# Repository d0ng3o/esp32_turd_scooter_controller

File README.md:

# Scooter control board

A standalone replacement control board for a **decommissioned Bird One #590AE**
shared e-scooter (the operator went bankrupt), built around a **Seeed XIAO
ESP32-C3**.

**Tested on:** a real **Bird One #590AE**, driving its stock **Nanjing Lishui
LSW6G-RF-FOC** motor controller over the original one-wire bus. Other Bird One
units (and other scooters on the same Lishui colon protocol) are likely
compatible but unverified.

> ⚠️ **Safety-critical, experimental, unofficial.** This board controls a
> vehicle's motor, throttle, and braking behavior. It is provided **as-is, with
> no warranty**, is not certified by anyone, and is not affiliated with or
> endorsed by Bird. Build and ride at your own risk — read
> **[DISCLAIMER.md](DISCLAIMER.md)** first.

The project has two halves:

1. **Reverse-engineering** the scooter's one-wire bus between the original
   control board and the Lishui motor controller — captured and documented so
   the controller can be driven directly.
2. A **custom KiCad control board** that replaces the dead original: same
   harness connector, same bus protocol, plus throttle/brake sensing, pack
   voltage, a buzzer, an addressable status LED, an on-board IMU for
   wake-on-motion, and an OLED display.

## Repository layout

```
.
├── PROTOCOL.md                 the reverse-engineered one-wire bus protocol
├── captures/                   raw bus captures backing PROTOCOL.md
├── esp32-scooter-schematic.html  interactive overview of the board
│
├── scooter_master.py           drive the motor controller as the bus master
├── pi_sniff.py                 passive ride logger (Raspberry Pi, RX-only)
├── bus_experiment.py           scripted bring-up probes
├── bus_listen_poll.py          poll at 50 Hz and log non-echo bytes
├── bus_soak.py                 long idle soak to catch slow telemetry fields
├── install_logger.sh           one-shot Pi logger installer
├── pi-scooter-logger.service   systemd unit for the Pi logger
│
├── firmware/                   the ESP-IDF firmware for the XIAO — see firmware/README.md
└── kicad/                      the hardware — see kicad/README.md
```

## The bus, briefly

Native **3.3 V open-drain half-duplex UART at 115200**. The control board is the
master: it polls the controller at 50 Hz with a colon-framed packet
(`':' TYPE LEN DATA[LEN] CHK CR LF`, `CHK` = XOR of the header+data) carrying the
throttle and light flags, and the controller answers with telemetry. Full frame
types, flags and field map are in **[PROTOCOL.md](PROTOCOL.md)**; it was all
confirmed on hardware (the PC drove the motor across the full throttle range).

## The hardware

The KiCad 10 design lives in **[kicad/](kicad/)** — see
[kicad/README.md](kicad/README.md) for the board overview,
[kicad/board/BOM.md](kicad/board/BOM.md) for the parts and full design
rationale, and [kicad/board/LAYOUT.md](kicad/board/LAYOUT.md) for the layout
playbook. The board is DRC-clean; bare boards and parts have been ordered.

## Status

- ✅ Bus protocol reverse-engineered and documented.
- ✅ Host/Pi tooling to drive and log the bus.
- ✅ Control board schematic + PCB complete, DRC-clean, ordered.
- ✅ ESP32-C3 firmware (ESP-IDF) in **[firmware/](firmware/)** — ride control,
  lights, lock/alarm, IMU wake, OLED UI, WiFi config/OTA; running on hardware.

## Note

The Python at the repo root is **host-side** tooling (PC / Raspberry Pi) used to
reverse-engineer and exercise the bus. It connects to the scooter via a USB
serial adapter (`scooter_master.py`, bench scripts) or a Pi UART (`pi_sniff.py`).
The firmware that runs on the XIAO itself lives in **[firmware/](firmware/)**.

## License

This project is **free/libre and strong-copyleft** — multi-licensed by component,
with each layer under a **share-alike** license. Anyone who copies, modifies, or
builds on it **must release their version under the same license** (no closed or
proprietary forks):

| Component | Files | License |
|---|---|---|
| Code / firmware / scripts | `*.py`, `*.sh`, `*.service` | **GPL-3.0-or-later** — [`LICENSE`](LICENSE) |
| Hardware design (original) | `kicad/board/`, original symbols/footprints | **CERN-OHL-S-2.0** — [`LICENSE-HARDWARE.txt`](LICENSE-HARDWARE.txt) |
| Documentation | `*.md`, BOMs, `esp32-scooter-schematic.html` | **CC-BY-SA-4.0** — [`LICENSE-DOCS.txt`](LICENSE-DOCS.txt) |

Copyright 2026 Taavi Laadung.

**Exception:** the vendor-sourced symbols, footprints, and 3D models under
`kicad/lcsc/` are **not** covered by the above and keep their original
LCSC/EasyEDA/manufacturer terms — see [`kicad/lcsc/README.md`](kicad/lcsc/README.md).

**CERN-OHL-S v2 notice (hardware):** *Copyright 2026 Taavi Laadung. This source
describes Open Hardware and is licensed under the CERN-OHL-S v2. You may
redistribute and modify this source and make products using it under the terms of
the CERN-OHL-S v2 (https://ohwr.org/cern_ohl_s_v2.txt). This source is distributed
WITHOUT ANY EXPRESS OR IMPLIED WARRANTY, INCLUDING OF MERCHANTABILITY,
SATISFACTORY QUALITY AND FITNESS FOR A PARTICULAR PURPOSE. Please see the
CERN-OHL-S v2 for applicable conditions. Source location:*
`https://github.com/d0ng3o/esp32_turd_scooter_controller` *(CERN-OHL-S requires the
source location to be conveyed and, where practicable, kept visible on the product
itself).*

## Disclaimer

See **[DISCLAIMER.md](DISCLAIMER.md)** for the full safety warning and the
"no affiliation" / reverse-engineering notices. In short: this is an
experimental, uncertified board that controls a vehicle — **build and ride at
your own risk**, and check your local road-traffic laws before using it.

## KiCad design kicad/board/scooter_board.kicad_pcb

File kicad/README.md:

# XIAO ESP32-C3 scooter control board — KiCad

Replacement control board for a decommissioned **Bird One #590AE** e-scooter.
A **Seeed XIAO ESP32-C3** reads the throttle and brake, talks to the Lishui
motor controller over the scooter's native **one-wire 3.3 V open-drain UART**
(115200), senses pack voltage, drives a buzzer and an addressable status LED,
carries an on-board IMU for wake-on-motion, and shows telemetry on an
enclosure-mounted OLED.

Designed in **KiCad 10**.

## Layout

```
kicad/
├── board/
│   ├── scooter_board.kicad_pro   project
│   ├── scooter_board.kicad_sch   schematic  ─┐ source of truth
│   ├── scooter_board.kicad_pcb   PCB         ─┘
│   ├── BOM.md                    bill of materials + full design rationale
│   ├── LAYOUT.md                 placement/routing playbook
│   ├── fp-lib-table              points at ../lcsc (the project footprint lib)
│   └── fabrication-toolkit-options.json
├── lcsc/                         project-local parts (LCSC-sourced)
│   ├── scooter_lcsc.kicad_sym    symbols
│   ├── scooter_lcsc.pretty/      footprints (6, all used by the board)
│   └── scooter_lcsc.3dshapes/    3D models for those footprints
├── lcsc_order_bom.csv            LCSC BOM-Tool upload (5 boards, no spares)
└── poop_logo.svg                 silkscreen art
```

Open `board/scooter_board.kicad_pro` in KiCad 10. The project footprint/symbol
libraries under `lcsc/` are referenced project-relative (`${KIPRJMOD}`), so the
board opens with all parts and 3D models intact — nothing to install.

## The board at a glance

- **2-layer, ~61 × 61 mm**, GND pour both sides with stitching vias.
- **MCU:** XIAO ESP32-C3 (U3), direct-solder castellated footprint.
- **Bus:** native 3.3 V open-drain half-duplex UART — D6 (OD TX) + D7 (RX) tied,
  100 Ω series (R6) to the harness, SMF3.3A TVS (D4) at the port. **No buffer IC.**
- **Analog:** throttle / brake / pack dividers → ADCs, 3.3 V zener clamps (D1–D3).
  Pack sense is on ADC2 (WiFi-coexistence caveat — see BOM.md).
- **IMU:** on-board LSM6DS3TR-C (U2, LGA-14), I²C, INT1 → D0 for deep-sleep
  wake-on-motion.
- **Outputs:** passive buzzer (BZ1 + Q1 low-side), WS2812B status LED (LED1, +5 V).
- **Connectors:** Amphenol 98424-F52-12ALF harness (J3), JST-GH to the off-board
  OLED (J4), 1×7 expansion header (J6, carries raw PACK_41V on pin 7).

Full part list, LCSC numbers, GPIO map, Amphenol pinout and the reasoning behind
every choice are in **[board/BOM.md](board/BOM.md)**. Layout/placement guidance is
in **[board/LAYOUT.md](board/LAYOUT.md)**.

## Ordering

Every placed part carries an `LCSC` field, so the project is the source of truth
for sourcing. Two paths:

- **Bare boards + self-assembly (current plan):** export Gerbers/drill from the
  PCB editor and order the bare board; order the parts from LCSC by uploading
  `lcsc_order_bom.csv` to the [LCSC BOM Tool](https://www.lcsc.com/bom).
- **JLC assembly:** generate a BOM + CPL with the Fabrication Toolkit plugin
  (part field = `LCSC`). Note U2 (LGA) and J3 (2 mm SMD) need hot-air/assembly.

Run **DRC** before ordering. The board is DRC-clean as committed.

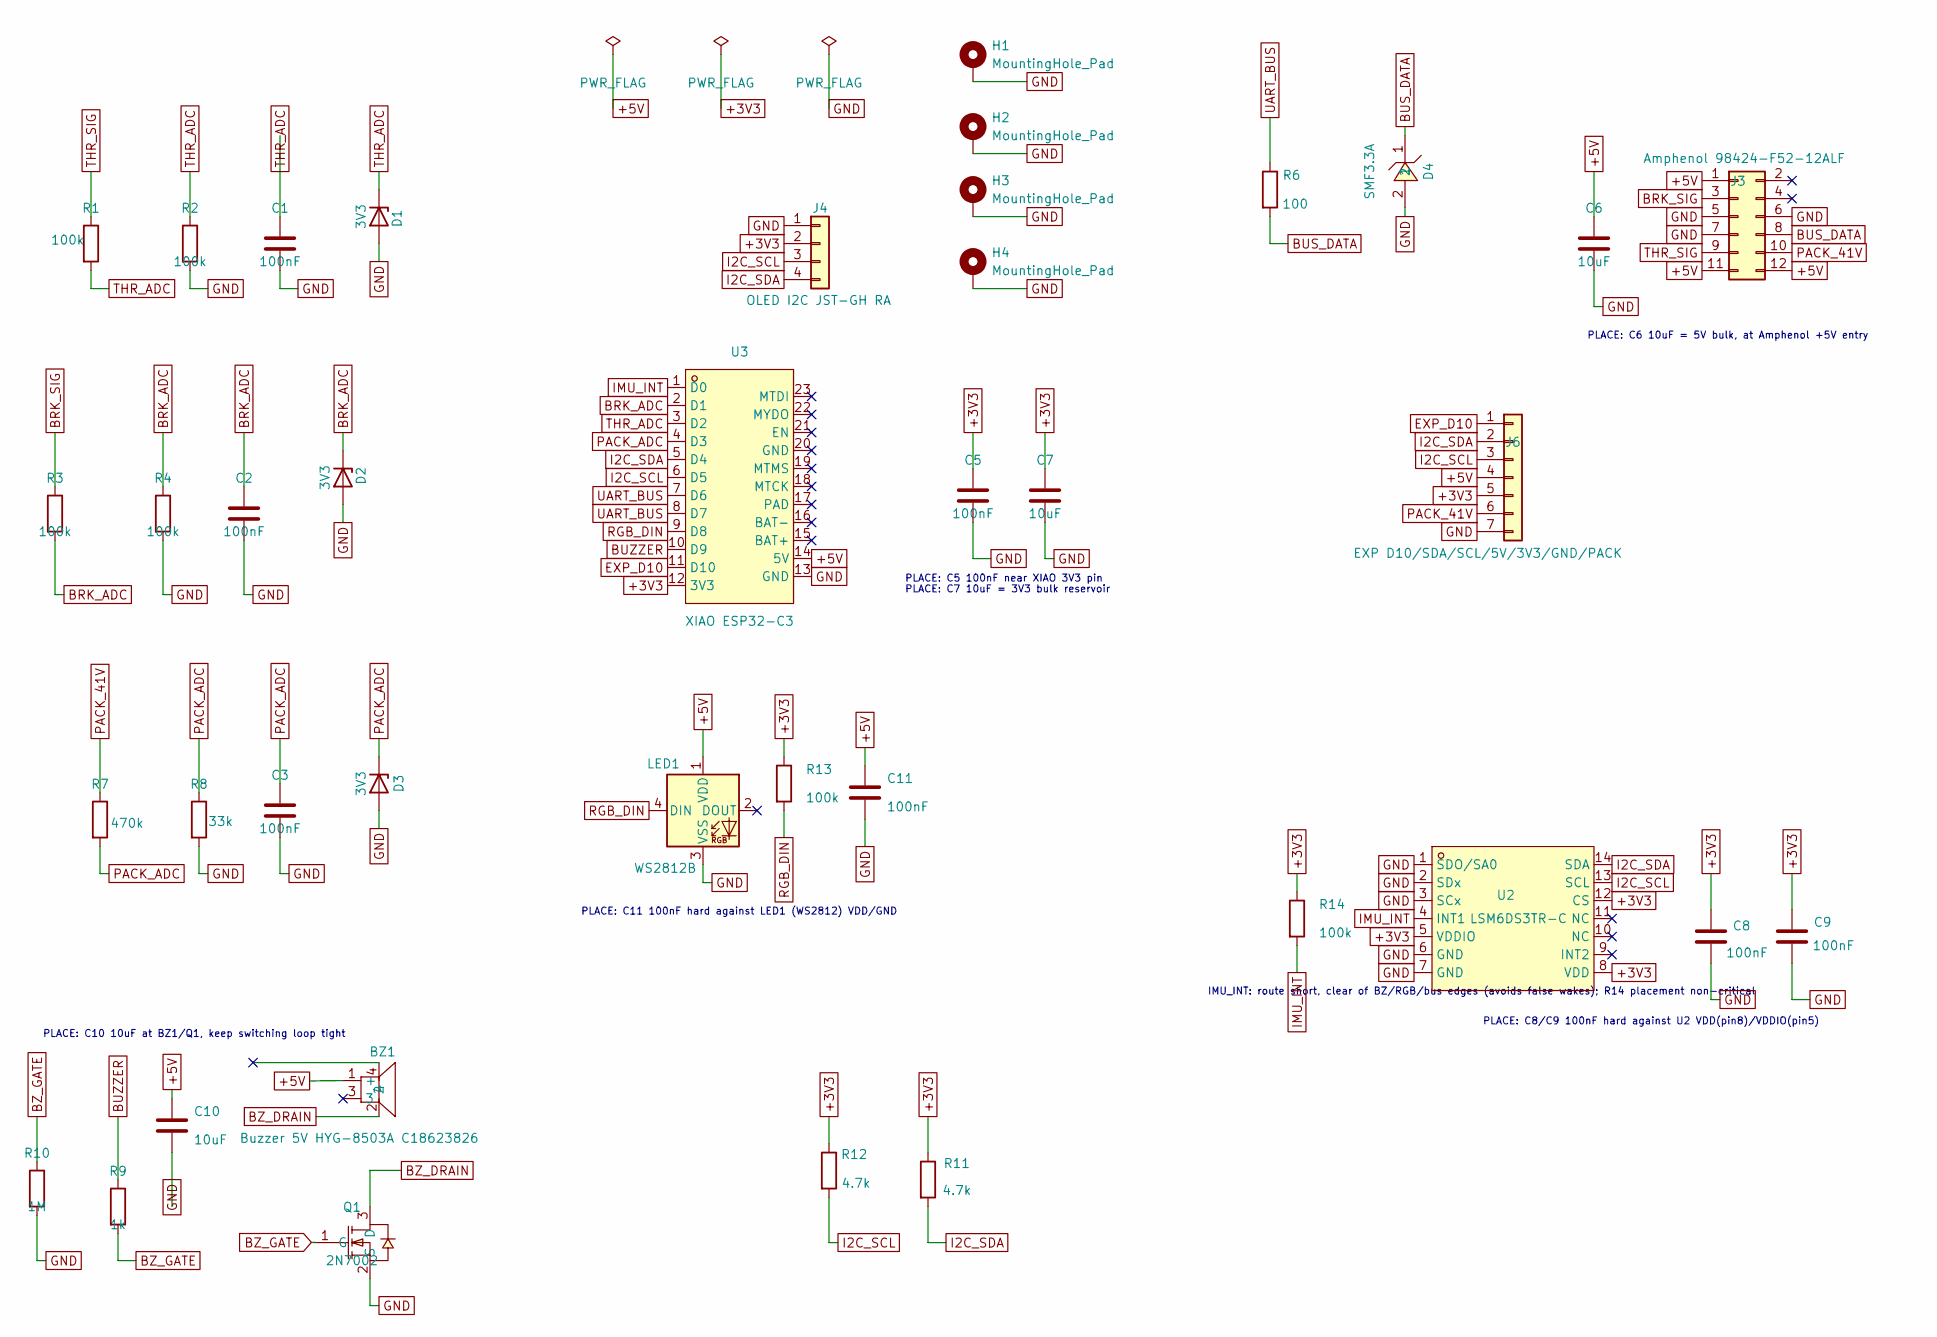
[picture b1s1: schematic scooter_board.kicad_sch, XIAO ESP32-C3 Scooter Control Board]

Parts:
BZ1: Buzzer 5V HYG-8503A C18623826; BUZ-SMD_4P-L8.5-W8.5-P8.50-TL-A; LCSC C18623826
C1, C2, C3, C5, C8, C9, C11: 100nF; C_0805_2012Metric; LCSC C49678
C6, C7, C10: 10uF; C_0805_2012Metric; LCSC C1713
D1, D2, D3: 3V3; D_SOD-123; LCSC C173413
D4: SMF3.3A; SOD-123_L2.8-W1.8-LS3.7-RD; LCSC C2917875
H1, H2, H3, H4: MountingHole_Pad; MountingHole_3.2mm_M3_DIN965_Pad_TopBottom
J3: Amphenol 98424-F52-12ALF; CONN-SMD_12P-P2.00-V-R2-C6-LS9.0; LCSC C239063
J4: OLED I2C JST-GH RA; JST_GH_SM04B-GHS-TB_1x04-1MP_P1.25mm_Horizontal; LCSC C189895
J6: EXP D10/SDA/SCL/5V/3V3/GND/PACK; PinHeader_1x07_P2.54mm_Vertical; LCSC C2337
LED1: WS2812B; LED_WS2812B_PLCC4_5.0x5.0mm_P3.2mm; LCSC C114586
Q1: 2N7002; SOT-23-3_L2.9-W1.3-P1.90-LS2.4-BR; LCSC C8545
R1, R2, R3, R4, R13, R14: 100k; R_0805_2012Metric; LCSC C17407
R6: 100; R_0805_2012Metric; LCSC C17408
R7: 470k; R_0805_2012Metric; LCSC C17709
R8: 33k; R_0805_2012Metric; LCSC C17633
R9: 1k; R_0805_2012Metric; LCSC C17513
R10: 1M; R_0805_2012Metric; LCSC C17514
R11, R12: 4.7k; R_0805_2012Metric; LCSC C17673
U2: LSM6DS3TR-C; LGA-14_L3.0-W2.5-P0.50-TL; LCSC C967633
U3: XIAO ESP32-C3; CONN-SMD_XIAO_ESP32C3; LCSC C19189385

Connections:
+3V3: C5.1, C7.1, C8.1, C9.1, J4.2, J6.5, R11.1, R12.1, R13.1, R14.1, U2.5 (VDDIO), U2.8 (VDD), U2.12 (CS), U3.12 (3V3)
+5V: BZ1.1 (+), C6.1, C10.1, C11.1, J3.1, J3.11, J3.12, J6.4, LED1.1 (VDD), U3.14 (5V)
BRK_ADC: C2.1, D2.1 (K), R3.2, R4.1, U3.2 (D1)
BRK_SIG: J3.3, R3.1
BUS_DATA: D4.1, J3.8, R6.2
BUZZER: R9.1, U3.10 (D9)
BZ_DRAIN: BZ1.2, Q1.3 (D)
BZ_GATE: Q1.1 (G), R9.2, R10.1
EXP_D10: J6.1, U3.11 (D10)
GND: C1.2, C2.2, C3.2, C5.2, C6.2, C7.2, C8.2, C9.2, C10.2, C11.2, D1.2 (A), D2.2 (A), D3.2 (A), D4.2, H1.1 (1_1), H2.1 (1_1), H3.1 (1_1), H4.1 (1_1), J3.5, J3.6, J3.7, J4.1, J6.7, LED1.3 (VSS), Q1.2 (S), R2.2, R4.2, R8.2, R10.2, U2.1 (SDO/SA0), U2.2 (SDx), U2.3 (SCx), U2.6 (GND), U2.7 (GND), U3.13 (GND)
I2C_SCL: J4.3, J6.3, R12.2, U2.13 (SCL), U3.6 (D5)
I2C_SDA: J4.4, J6.2, R11.2, U2.14 (SDA), U3.5 (D4)
IMU_INT: R14.2, U2.4 (INT1), U3.1 (D0)
PACK_41V: J3.10, J6.6, R7.1
PACK_ADC: C3.1, D3.1 (K), R7.2, R8.1, U3.4 (D3)
RGB_DIN: LED1.4 (DIN), R13.2, U3.9 (D8)
THR_ADC: C1.1, D1.1 (K), R1.2, R2.1, U3.3 (D2)
THR_SIG: J3.9, R1.1
UART_BUS: R6.1, U3.7 (D6), U3.8 (D7)

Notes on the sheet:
PLACE: C10 10uF at BZ1/Q1, keep switching loop tight
PLACE: C7 10uF = 3V3 bulk reservoir
PLACE: C8/C9 100nF hard against U2 VDD(pin8)/VDDIO(pin5)
PLACE: C5 100nF near XIAO 3V3 pin
PLACE: C6 10uF = 5V bulk, at Amphenol +5V entry
PLACE: C11 100nF hard against LED1 (WS2812) VDD/GND
IMU_INT: route short, clear of BZ/RGB/bus edges (avoids false wakes); R14 placement non-critical

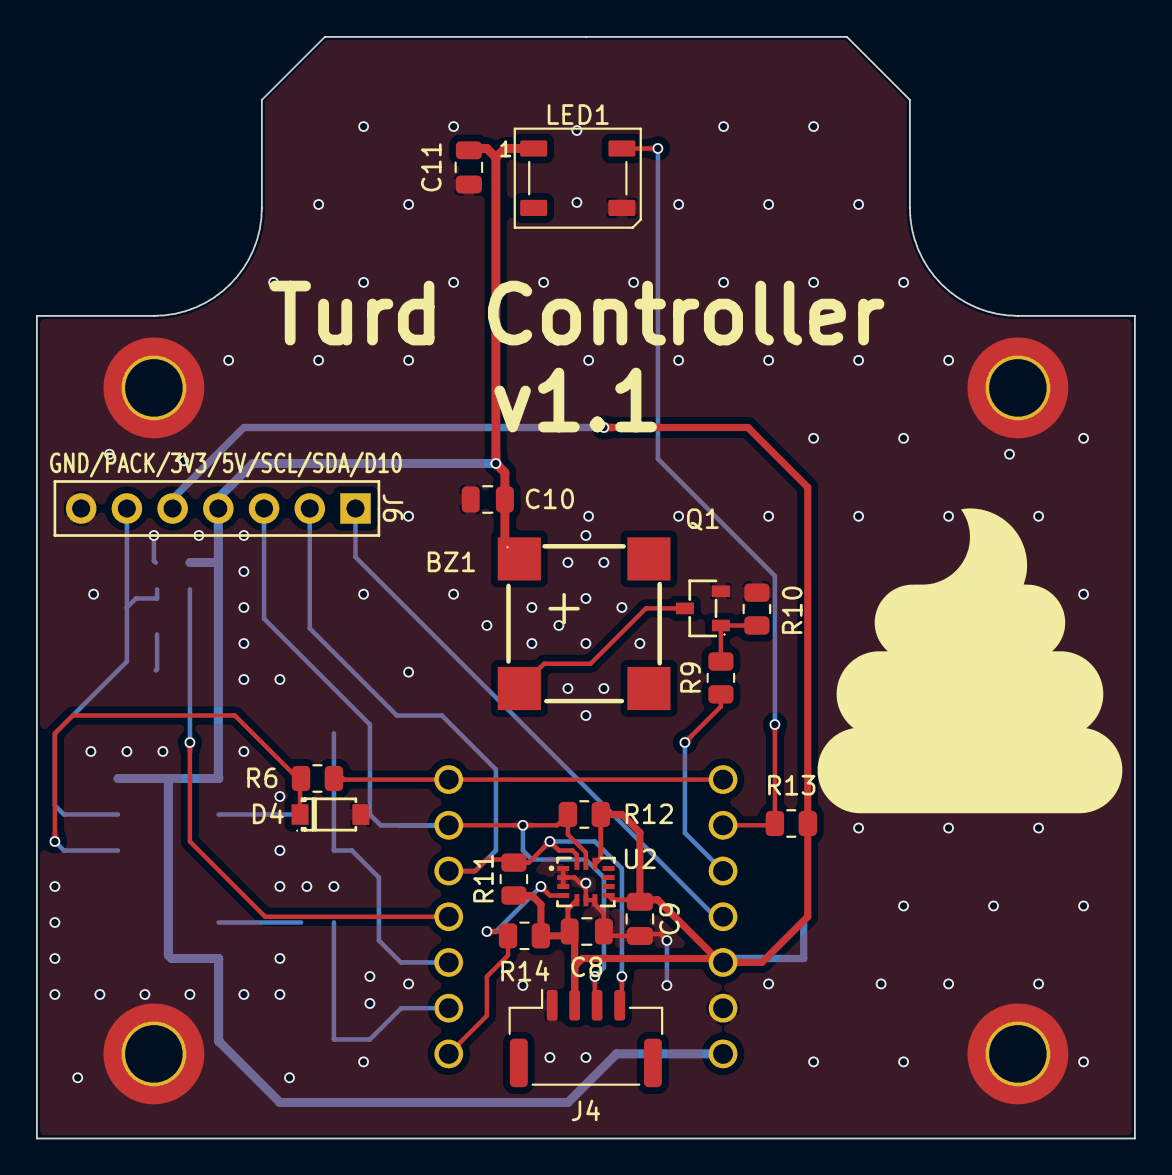
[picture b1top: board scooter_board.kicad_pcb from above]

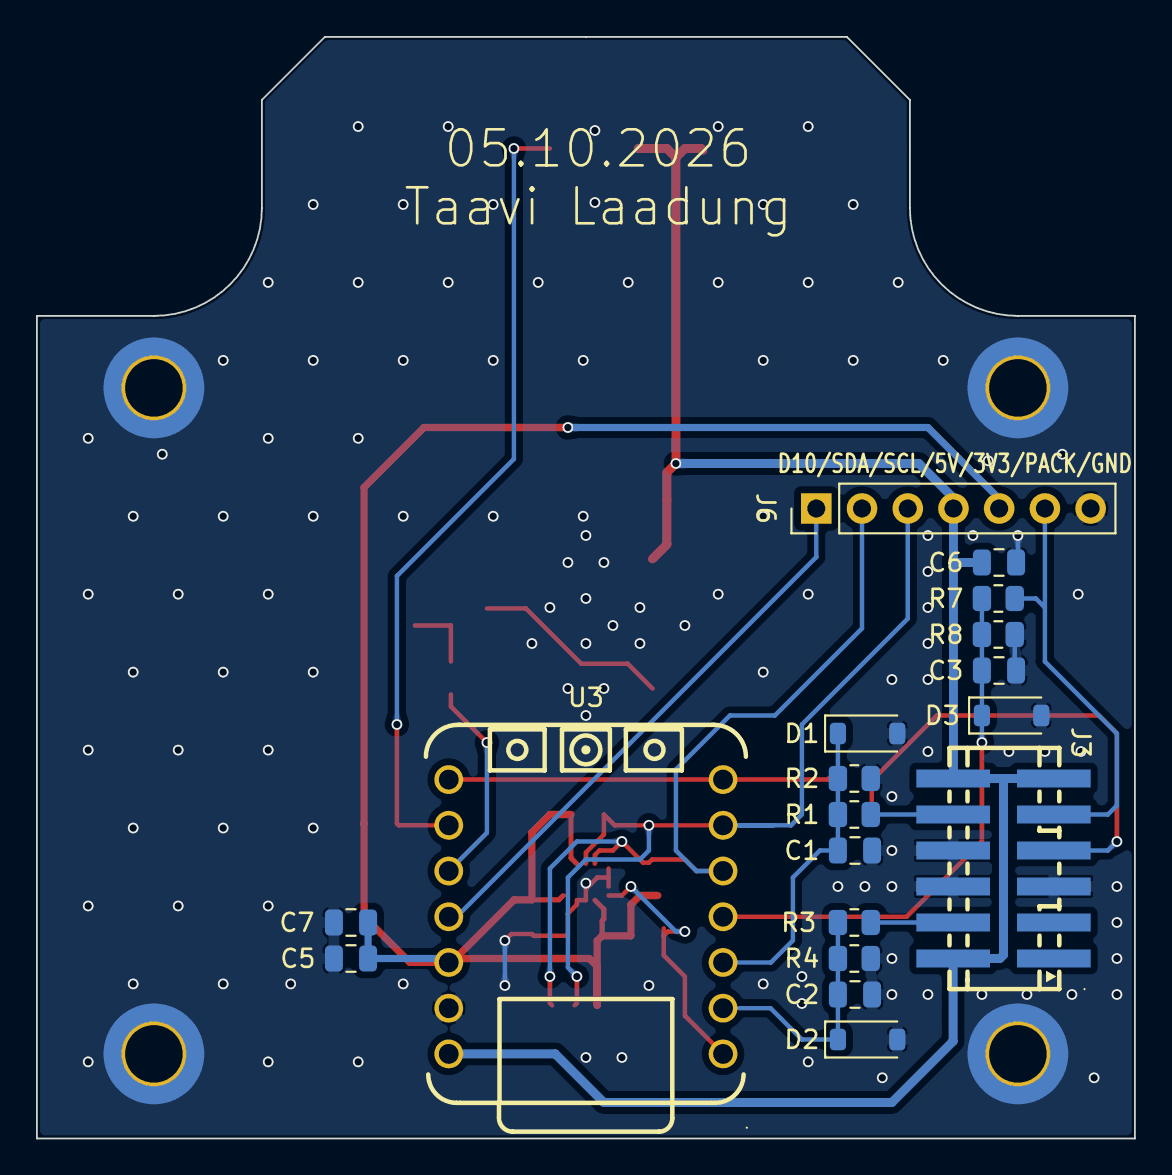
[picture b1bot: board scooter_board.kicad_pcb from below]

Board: 2 copper layers, 61.0 x 61.2 mm, 39 parts (18 on the bottom side), 19 nets.

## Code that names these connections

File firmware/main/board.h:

// SPDX-License-Identifier: GPL-3.0-or-later
// Copyright 2026 Taavi Laadung
//
// board.h - one place for the XIAO ESP32-C3 pin map and firmware tunables.
// Silk labels (D0..D10) are the XIAO's; GPIOs are the ESP32-C3's.

#pragma once

#include "driver/gpio.h"
#include "hal/adc_types.h"
#include "driver/uart.h"

// ---- Pin map (XIAO silk -> GPIO) --------------------------------------------
#define PIN_IMU_INT       GPIO_NUM_2    // D0  IMU INT1 / deep-sleep wake
#define PIN_BRAKE_ADC     GPIO_NUM_3    // D1  brake input     (ADC1_CH3)
#define PIN_THROTTLE_ADC  GPIO_NUM_4    // D2  throttle input  (ADC1_CH4)
#define PIN_PACK_ADC      GPIO_NUM_5    // D3  pack sense      (ADC2_CH0, WiFi-gated)
#define PIN_I2C_SDA       GPIO_NUM_6    // D4  OLED + IMU
#define PIN_I2C_SCL       GPIO_NUM_7    // D5  OLED + IMU
#define PIN_BUS_TX        GPIO_NUM_21   // D6  one-wire bus TX (open-drain)
#define PIN_BUS_RX        GPIO_NUM_20   // D7  one-wire bus RX (tied to D6)
#define PIN_WS2812        GPIO_NUM_8    // D8  status LED data
#define PIN_BUZZER        GPIO_NUM_9    // D9  buzzer (low-side MOSFET gate)
#define PIN_EXPANSION     GPIO_NUM_10   // D10 expansion header (unused in fw)

// ---- ADC channels (ESP32-C3) ------------------------------------------------
#define ADC_BRAKE_CHANNEL     ADC_CHANNEL_3   // GPIO3  (ADC1)
#define ADC_THROTTLE_CHANNEL  ADC_CHANNEL_4   // GPIO4  (ADC1)
#define ADC_PACK_CHANNEL      ADC_CHANNEL_0   // GPIO5  (ADC2 - blocked while WiFi runs)

// Pack voltage divider: R7 (top) / R8 (bottom). Vpack = Vnode * (top+bot)/bot.
#define PACK_DIV_R_TOP        470000          // R7
#define PACK_DIV_R_BOT        33000           // R8

// ---- One-wire bus -----------------------------------------------------------
#define BUS_UART_NUM      UART_NUM_1
#define BUS_BAUD          115200
#define POLL_PERIOD_MS    20             // 50 Hz heartbeat (PROTOCOL.md 3.1/5.2)
#define STATUS_EVERY_N    5              // request status on every 5th poll
#define BUS_LINK_TIMEOUT_US  300000      // no status for 300 ms => link lost
#define BUS_LINK_ALERT_REARM_US 1000000  // link must be up this long to re-arm the loss chirp

// ---- Charging ---------------------------------------------------------------
#define CHARGE_DETECT_cA     5           // charge_cA (0.01 A) above this => charger active (~0.05 A)
#define CHARGE_FULL_SOC      100         // soc (%) at/above this while charging => battery full
#define CHARGE_SCREEN_ON_MS  15000       // keep the OLED on this long after motion while charging

// ---- Buzzer -----------------------------------------------------------------
#define BUZZER_TONE_HZ    2700           // HYG-8503A is loudest near 2.7 kHz

// ---- Throttle / brake input (RAW 12-bit ADC endpoints) ----------------------
// Placeholder calibration until the real harness is on the bench. The dividers
// (R1-R4, 100k) halve the hall signal; these get replaced by a runtime
// calibration (serial-triggered) and NVS storage in a later phase.
#define THROTTLE_RAW_MIN  600            // released
#define THROTTLE_RAW_MAX  2600           // full
#define BRAKE_RAW_MIN     600            // released
#define BRAKE_RAW_MAX     2600           // full
#define THROTTLE_DEADZONE_PCT  5         // ignore the bottom 5 % of travel
#define BRAKE_ACTIVE_PCT       40        // brake "on" past ~40 % travel (PROTOCOL.md 6.3)

// ---- Control ----------------------------------------------------------------
#define THROTTLE_CMD_MAX  255            // cap sent to controller (0..255)

// ---- Gestures (percent of throttle travel; evaluated only while stationary) --
// Unlock/lock toggle: hold brake + blip the throttle GEST_TRIPLE_COUNT times.
#define GEST_BLIP_HIGH_PCT     60        // throttle must exceed this to start a blip
#define GEST_BLIP_LOW_PCT      10        // ...then drop below this to complete it
#define GEST_TRIPLE_COUNT       3
#define GEST_TRIPLE_WINDOW_MS  3000      // all blips must land within this window
// Config/OTA mode: hold brake + full throttle continuously for this long.
#define GEST_CONFIG_HIGH_PCT   90
#define GEST_CONFIG_HOLD_MS   20000      // 20 s (deliberately awkward)
